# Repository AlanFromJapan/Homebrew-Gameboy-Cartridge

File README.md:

Homebrew-Gameboy-Cartridge
==========================

**This is my fork of the original project**

To make it work (as a 32kB cartridge): check the  manual on my website http://electrogeek.cc/gameboy%20homebrew%20cartridge.html

---

Eagle library, schematic, and board files for a Gameboy Cartridge PCB that uses a Atmel AT49F040 to replace the ROM in a Gameboy cartridge.

Based on Gerry O'Brien's work on a D.I.Y. 512Kb NINTENDO Game Boy Flash Cartridge. 
http://www.digital-circuitry.com/GameBoy.htm

This work is licensed under a Creative Commons Attribution 3.0 Unported License.

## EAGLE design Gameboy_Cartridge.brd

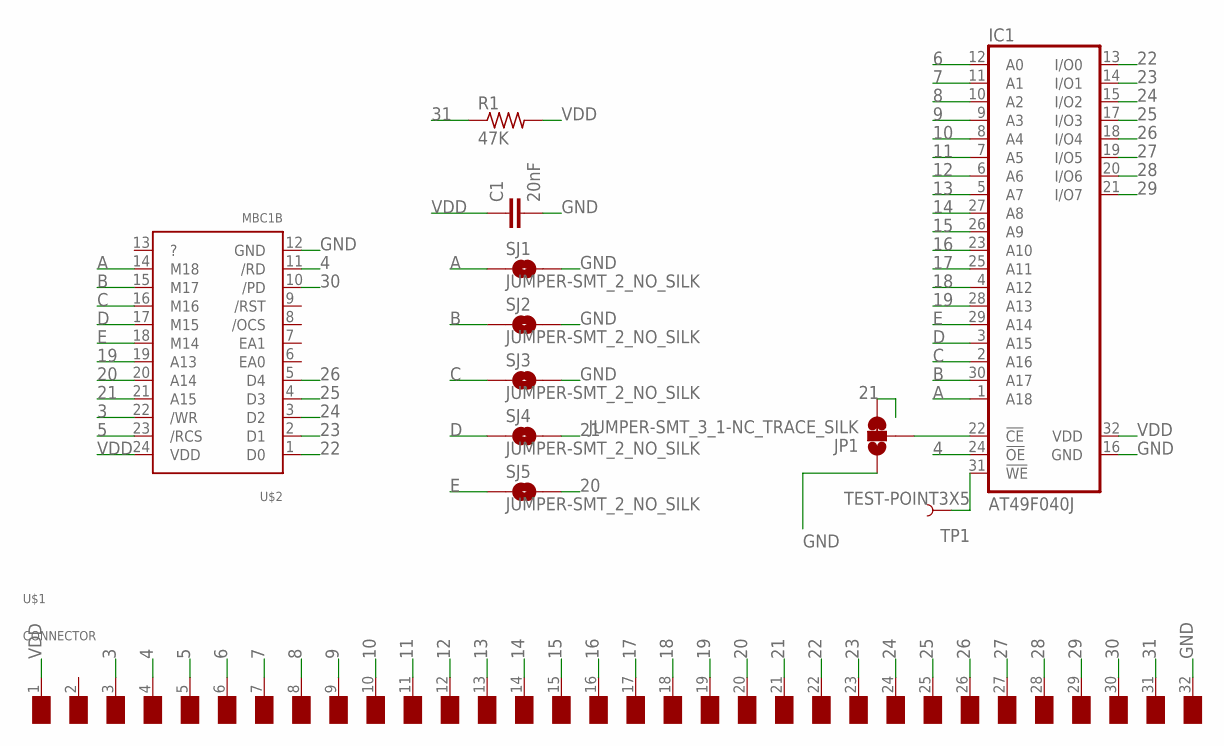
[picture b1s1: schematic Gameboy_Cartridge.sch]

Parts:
C1: 20nF; C0805
IC1: AT49F040J; PLCC32R
JP1: JUMPER-SMT_3_1-NC_TRACE_SILK; SMT-JUMPER_3_1-NC_TRACE_SILK
R1: 47K; M0805
SJ1, SJ2, SJ3, SJ4, SJ5: JUMPER-SMT_2_NO_SILK; SMT-JUMPER_2_NO_SILK
TP1: TEST-POINT3X5; PAD.03X.05
U$1: CONNECTOR
U$2: MBC1B

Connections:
3: U$1.3 (/WR), U$2.22 (/WR)
4: IC1.24 (!OE), U$1.4 (/RD), U$2.11 (/RD)
5: U$1.5 (/RCS), U$2.23 (/RCS)
6: IC1.12 (A0), U$1.6 (A0)
7: IC1.11 (A1), U$1.7 (A1)
8: IC1.10 (A2), U$1.8 (A2)
9: IC1.9 (A3), U$1.9 (A3)
10: IC1.8 (A4), U$1.10 (A4)
11: IC1.7 (A5), U$1.11 (A5)
12: IC1.6 (A6), U$1.12 (A6)
13: IC1.5 (A7), U$1.13 (A7)
14: IC1.27 (A8), U$1.14 (A8)
15: IC1.26 (A9), U$1.15 (A9)
16: IC1.23 (A10), U$1.16 (A10)
17: IC1.25 (A11), U$1.17 (A11)
18: IC1.4 (A12), U$1.18 (A12)
19: IC1.28 (A13), U$1.19 (A13), U$2.19 (A13)
20: SJ5.2, U$1.20 (A14), U$2.20 (A14)
21: JP1.3, SJ4.2, U$1.21 (A15), U$2.21 (A15)
22: IC1.13 (I/O0), U$1.22 (D0), U$2.1 (D0)
23: IC1.14 (I/O1), U$1.23 (D1), U$2.2 (D1)
24: IC1.15 (I/O2), U$1.24 (D2), U$2.3 (D2)
25: IC1.17 (I/O3), U$1.25 (D3), U$2.4 (D3)
26: IC1.18 (I/O4), U$1.26 (D4), U$2.5 (D4)
27: IC1.19 (I/O5), U$1.27 (D5)
28: IC1.20 (I/O6), U$1.28 (D6)
29: IC1.21 (I/O7), U$1.29 (D7)
30: U$1.30 (/RS), U$2.10 (/PD)
31: R1.1, U$1.31 (VIN)
A: IC1.1 (A18), SJ1.1, U$2.14 (M18)
B: IC1.30 (A17), SJ2.1, U$2.15 (M17)
C: IC1.2 (A16), SJ3.1, U$2.16 (M16)
D: IC1.3 (A15), SJ4.1, U$2.17 (M15)
E: IC1.29 (A14), SJ5.1, U$2.18 (M14)
GND: C1.2, IC1.16 (GND), JP1.1, SJ1.2, SJ2.2, SJ3.2, U$1.32 (GND), U$2.12 (GND)
unnamed: IC1.31 (!WE), TP1.P$1
unnamed: IC1.22 (!CE), JP1.2
VDD: C1.1, IC1.32 (VDD), R1.2, U$1.1 (VDD), U$2.24 (VDD)

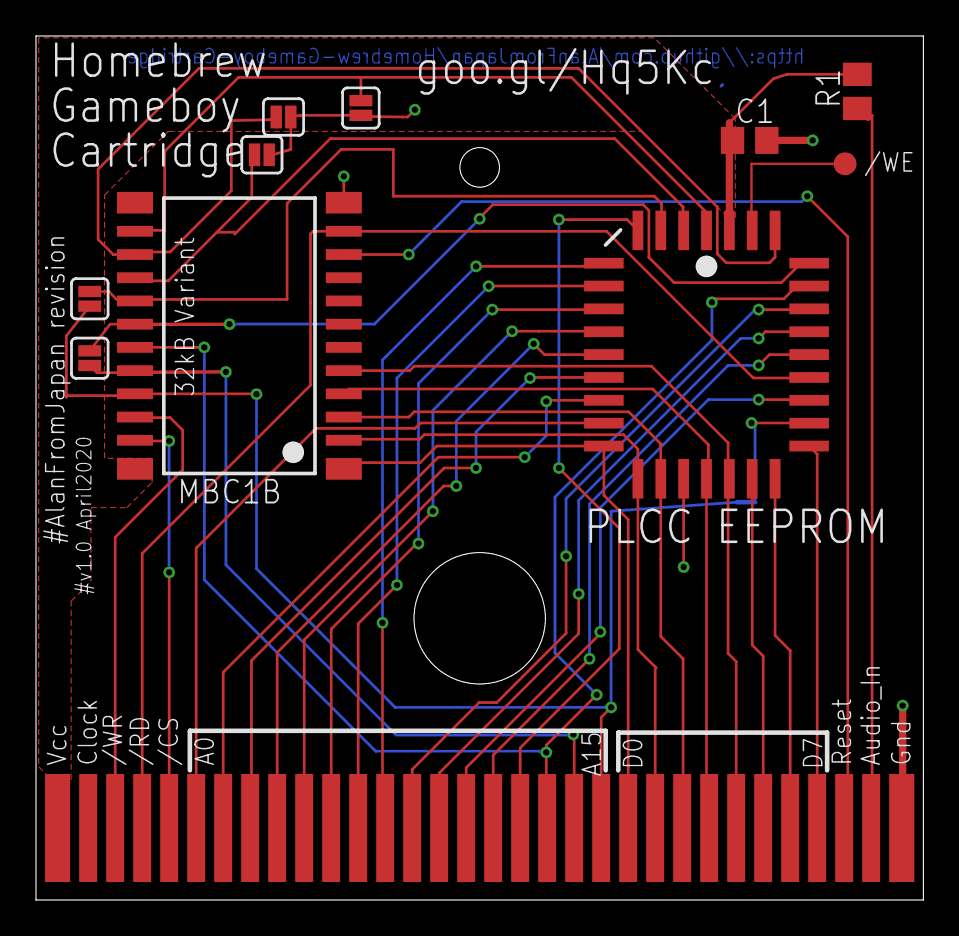
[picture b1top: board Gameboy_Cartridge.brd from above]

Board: 2 copper layers, 49.3 x 48.0 mm, 12 parts (1 on the bottom side), 38 nets.

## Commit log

2020-04-04 Moved solder jumper outside of the DMG01 chip.
2020-04-04 Changed a few details, hope I didn't screw it up...
2020-04-05 sent to production, hope it will work.
2020-04-29 Doesn't work as is now :(
2020-04-30 Added comments and drawings

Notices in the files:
parts and their libraries:
SparkFun-Jumpers: Licensing: Creative Commons ShareAlike 4.0 International - https://creativecommons.org/licenses/by-sa/4.0
